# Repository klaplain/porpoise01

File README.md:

# UnderwaterAcoustics
This is the code required for the Underwater Acoustics STM32 Acquisition SubSystem that works with the Porpoise01 board and the Raspberry Pi

main.c contains the necessary code to acquire an analog signal sampling at about 700kHz and storing the result to a .DAT file that contains the analog values.  Although the file has a WAV file header, the values are 16 bit unsigned values so the DAT file needs to be post-processed to convert it to a WAV file.  This post-processing is done when saving to the raspberry pi.

*.ioc contains all the necessary CubeIDE configuration data

uw_acoust_client.py is the app that runs on the raspberry pi and controls the Seeed STM32 acquisition system

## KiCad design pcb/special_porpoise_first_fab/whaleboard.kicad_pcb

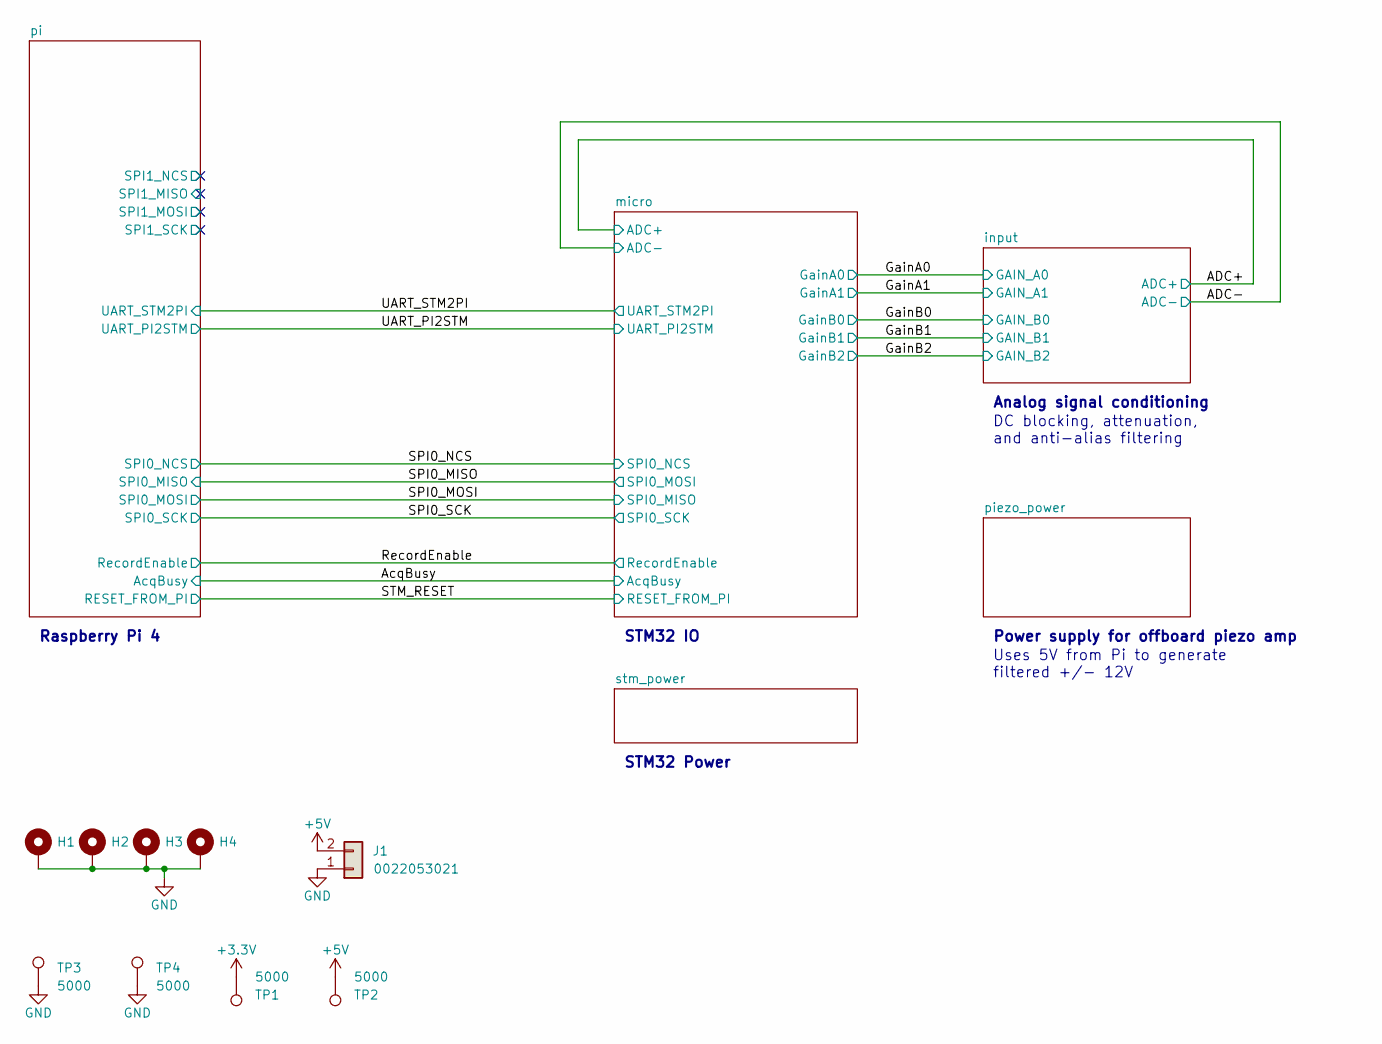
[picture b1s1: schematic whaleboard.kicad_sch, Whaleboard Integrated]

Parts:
H1, H2, H3, H4: MountingHole_Pad; MountingHole_2.7mm_Pad
J1: 0022053021; Molex_KK-254_AE-6410-02A_1x02_P2.54mm_Vertical; DIGI 900-0022053021-ND
TP1, TP2, TP3, TP4: 5000; TestPoint_Keystone_5000-5004_Miniature

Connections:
+3.3V: TP1.1; also elsewhere on the board
+5V: J1.2, TP2.1; also elsewhere on the board
GND: H1.1, H2.1, H3.1, H4.1, J1.1, TP3.1, TP4.1; also elsewhere on the board

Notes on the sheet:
Uses 5V from Pi to generate filtered +/- 12V
Analog signal conditioning
STM32 IO
STM32 Power
DC blocking, attenuation, and anti-alias filtering
Raspberry Pi 4
Power supply for offboard piezo amp

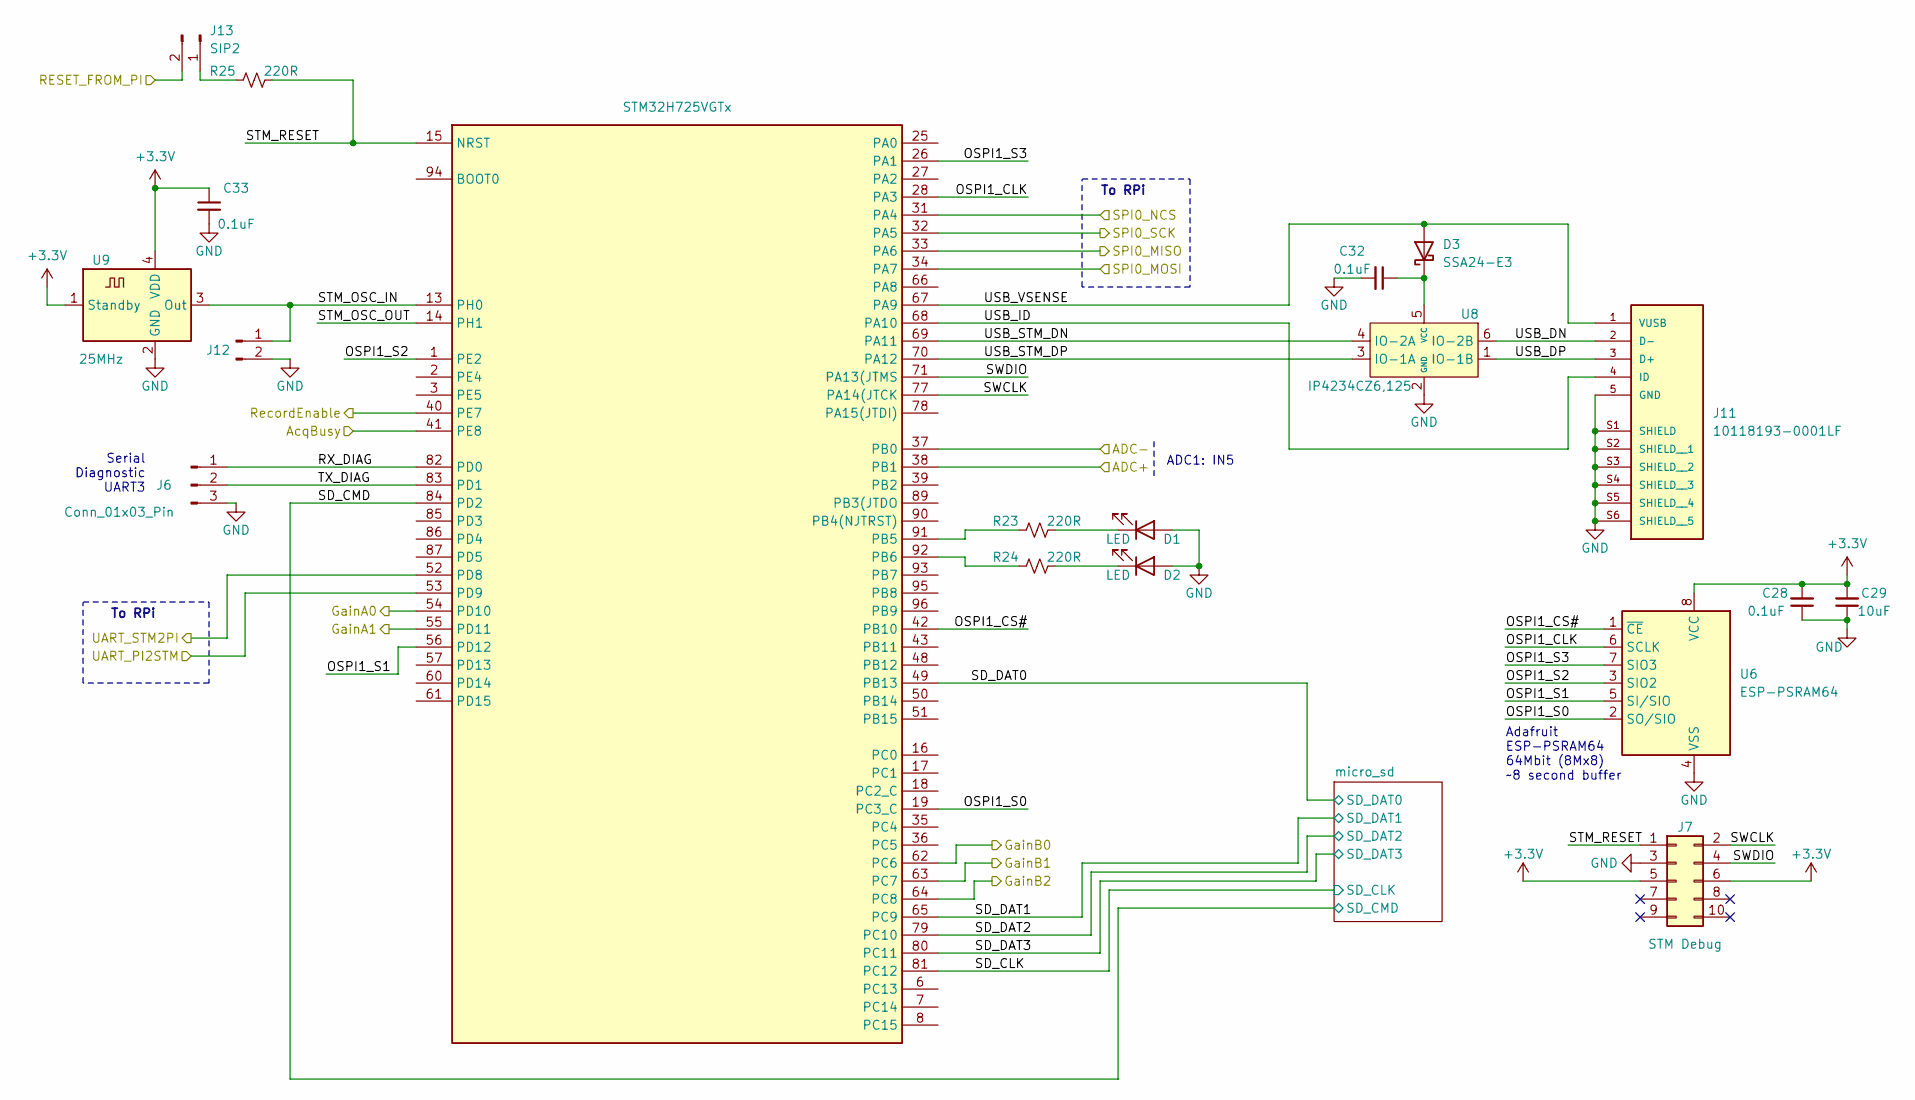
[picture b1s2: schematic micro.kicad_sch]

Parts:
C28, C32, C33: 0.1uF; C_0603_1608Metric; DIGI 1276-1000-1-ND
C29: 10uF; C_0805_2012Metric; DIGI 1276-1096-1-ND
D1, D2: LED; LED_0805_2012Metric; DIGI 3147-B1701UY--20D000214U1930CT-ND
D3: SSA24-E3; D_SMA; DIGI SSA24-E3/61TGICT-ND
J6: Conn_01x03_Pin; PinHeader_1x03_P2.54mm_Vertical
J7: STM Debug; PinSocket_2x05_P2.54mm_Vertical; DIGI S9194-ND
J11: 10118193-0001LF; AMPHENOL_10118193-0001LF; PARTREV E; DIGI 609-4616-1-ND
J12: Conn_01x02_Pin; PinHeader_1x02_P2.00mm_Vertical
J13: SIP2; PinHeader_1x02_P2.54mm_Vertical
R23, R24, R25: 220R; R_0603_1608Metric
U6: ESP-PSRAM64; SOIC-8_3.9x4.9mm_P1.27mm; DIGI 1528-4677-ND
U7: STM32H725VGTx; LQFP-100_14x14mm_P0.5mm
U8: IP4234CZ6,125; TSOP-6_1.65x3.05mm_P0.95mm; DIGI 1727-4717-1-ND
U9: 25MHz; Oscillator_SMD_Abracon_ASDMB-4Pin_2.5x2.0mm; DIGI 535-ATX-H12-F-25.000MHZ-G100-TCT-ND

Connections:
+3.3V: C28.2, C29.2, C33.1, J7.5, J7.6, U6.8 (VCC), U9.1 (Standby), U9.4 (VDD); also elsewhere on the board
/ADC+: U7.38 (PB1); also elsewhere on the board
/ADC-: U7.37 (PB0); also elsewhere on the board
/AcqBusy: U7.41 (PE8); also elsewhere on the board
/GainA0: U7.54 (PD10); also elsewhere on the board
/GainA1: U7.55 (PD11); also elsewhere on the board
/GainB0: U7.62 (PC6); also elsewhere on the board
/GainB1: U7.63 (PC7); also elsewhere on the board
/GainB2: U7.64 (PC8); also elsewhere on the board
/RecordEnable: U7.40 (PE7); also elsewhere on the board
/SPI0_MISO: U7.34 (PA7); also elsewhere on the board
/SPI0_MOSI: U7.33 (PA6); also elsewhere on the board
/SPI0_NCS: U7.31 (PA4); also elsewhere on the board
/SPI0_SCK: U7.32 (PA5); also elsewhere on the board
/STM_RESET: J13.2; also elsewhere on the board
/UART_PI2STM: U7.53 (PD9); also elsewhere on the board
/UART_STM2PI: U7.52 (PD8); also elsewhere on the board
/micro/OSPI1_CLK: U6.6 (SCLK), U7.28 (PA3)
/micro/OSPI1_CS#: U6.1 (~CE), U7.42 (PB10)
/micro/OSPI1_S0: U6.2 (SO/SIO), U7.19 (PC3_C)
/micro/OSPI1_S1: U6.5 (SI/SIO), U7.56 (PD12)
/micro/OSPI1_S2: U6.3 (SIO2), U7.1 (PE2)
/micro/OSPI1_S3: U6.7 (SIO3), U7.26 (PA1)
/micro/RX_DIAG: J6.1, U7.82 (PD0)
/micro/SD_CLK: U7.81 (PC12); also elsewhere on the board
/micro/SD_CMD: U7.84 (PD2); also elsewhere on the board
/micro/SD_DAT0: U7.49 (PB13); also elsewhere on the board
/micro/SD_DAT1: U7.65 (PC9); also elsewhere on the board
/micro/SD_DAT2: U7.79 (PC10); also elsewhere on the board
/micro/SD_DAT3: U7.80 (PC11); also elsewhere on the board
/micro/STM_OSC_IN: J12.1, U7.13 (PH0), U9.3 (Out)
/micro/STM_OSC_OUT: U7.14 (PH1)
/micro/STM_RESET: J7.1, R25.2, U7.15 (NRST)
/micro/SWCLK: J7.2, U7.77 (PA14(JTCK)
/micro/SWDIO: J7.4, U7.71 (PA13(JTMS)
/micro/TX_DIAG: J6.2, U7.83 (PD1)
/micro/USB_DN: J11.2 (D-), U8.6 (IO-2B)
/micro/USB_DP: J11.3 (D+), U8.1 (IO-1B)
/micro/USB_ID: J11.4 (ID), U7.68 (PA10)
/micro/USB_STM_DN: U7.69 (PA11), U8.4 (IO-2A)
/micro/USB_STM_DP: U7.70 (PA12), U8.3 (IO-1A)
/micro/USB_VSENSE: D3.2 (A), J11.1 (VUSB), U7.67 (PA9)
GND: C28.1, C29.1, C32.2, C33.2, D1.2 (A), D2.2 (A), J6.3, J7.3, J11.5 (GND), J11.S1 (SHIELD), J11.S2 (SHIELD__1), J11.S3 (SHIELD__2), J11.S4 (SHIELD__3), J11.S5 (SHIELD__4), J11.S6 (SHIELD__5), J12.2, U6.4 (VSS), U8.2 (GND), U9.2 (GND); also elsewhere on the board
unnamed: D1.1 (K), R23.2
unnamed: D2.1 (K), R24.2
unnamed: C32.1, D3.1 (K), U8.5 (VCC)
unnamed: J13.1, R25.1
unnamed: R23.1, U7.91 (PB5)
unnamed: R24.1, U7.92 (PB6)

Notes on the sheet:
Adafruit ESP-PSRAM64 64Mbit (8Mx8) ~8 second buffer
Serial Diagnostic UART3
ADC1: IN5
To RPi

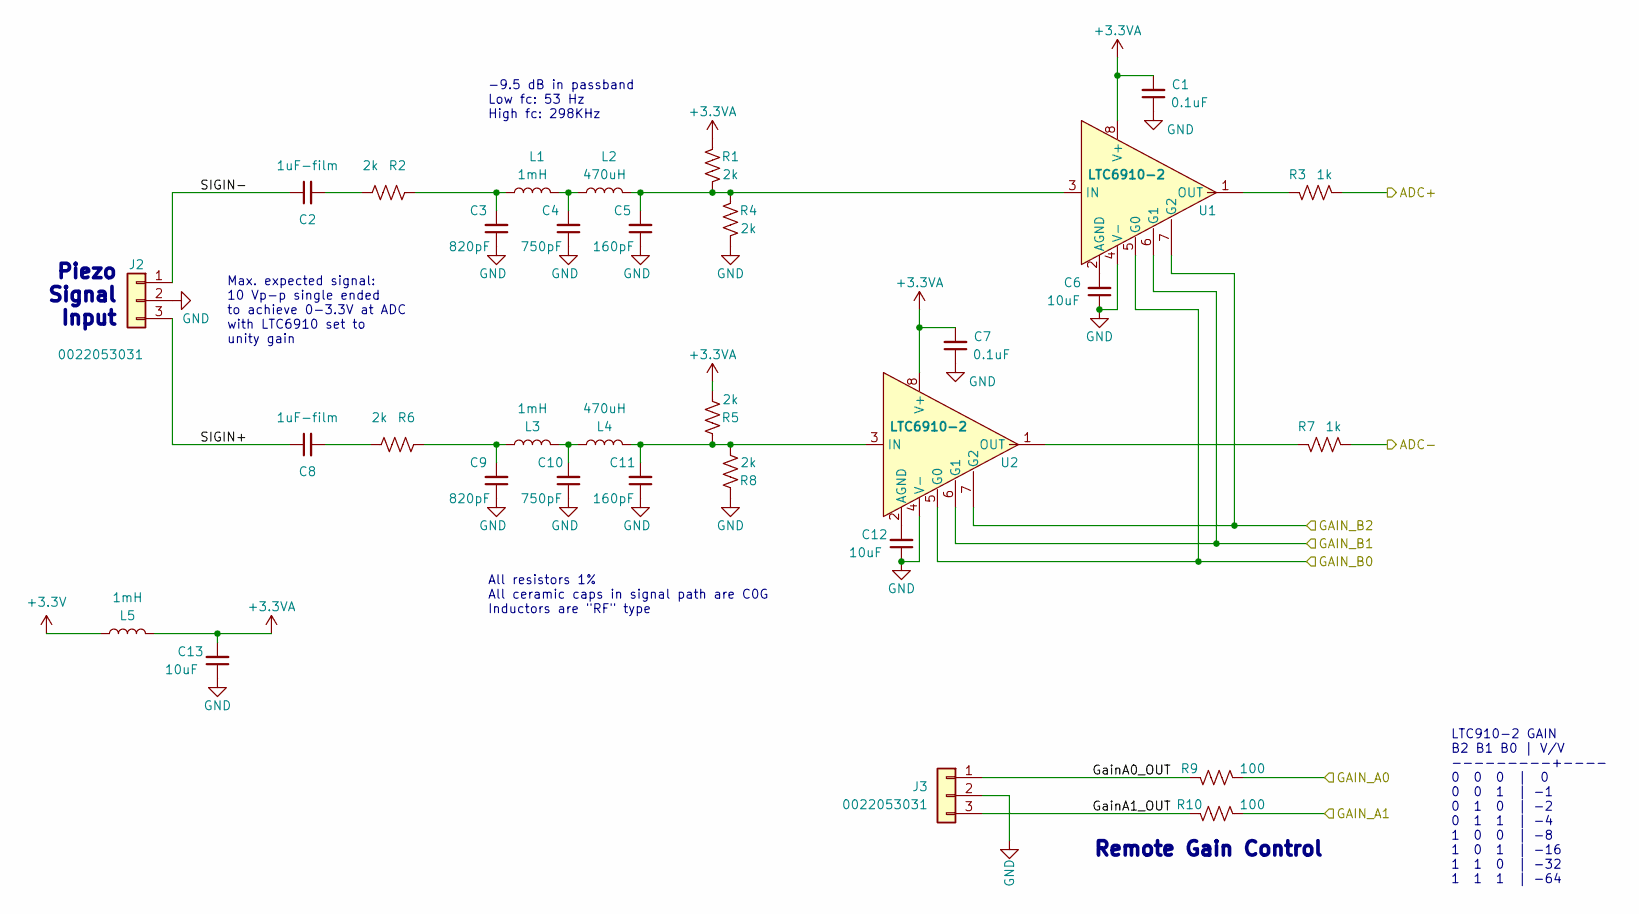
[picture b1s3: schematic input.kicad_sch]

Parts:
C1, C7: 0.1uF; C_0603_1608Metric; DIGI 1276-1000-1-ND
C2, C8: 1uF-film; C_2220_5750Metric; DIGI 399-LDECD4100MA0N00CT-ND
C3, C9: 820pF; C_1206_3216Metric; DIGI 478-KGM31BCG2A821JTCT-ND
C4, C10: 750pF; C_1206_3216Metric; DIGI 399-14711-1-ND
C5, C11: 160pF; C_0603_1608Metric; DIGI 399-15367-1-ND
C6, C12, C13: 10uF; C_0805_2012Metric; DIGI 1276-1096-1-ND
J2, J3: 0022053031; CONN_A-7478-03A_MOL; DIGI WM4301-ND
L1, L3, L5: 1mH; L_1812_4532Metric_Pad1.30x3.40mm_HandSolder; DIGI CM453232-102JLCT-ND
L2, L4: 470uH; L_1812_4532Metric_Pad1.30x3.40mm_HandSolder; DIGI 118-CM453232-471JLCT-ND
R1, R2, R4, R5, R6, R8: 2k; R_0603_1608Metric; DIGI RC0603FR-072KL
R3, R7: 1k; R_0603_1608Metric; DIGI 311-1.00KHRCT-ND
R9, R10: 100; R_0603_1608Metric; DIGI 311-100HRCT-ND
U1, U2: LTC6910-2; TSOT-23-8; DIGI 161-LTC6910-2ITS8#TRPBFCT-ND

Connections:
+3.3V: L5.1; also elsewhere on the board
+3.3VA: C1.2, C7.2, C13.2, L5.2, R1.2, R5.1, U1.8 (V+), U2.8 (V+)
/ADC+: R3.1; also elsewhere on the board
/ADC-: R7.1; also elsewhere on the board
/GainA0: R9.1; also elsewhere on the board
/GainA1: R10.1; also elsewhere on the board
/GainB0: U1.5 (G0), U2.5 (G0); also elsewhere on the board
/GainB1: U1.6 (G1), U2.6 (G1); also elsewhere on the board
/GainB2: U1.7 (G2), U2.7 (G2); also elsewhere on the board
/input/GainA0_OUT: J3.1, R9.2
/input/GainA1_OUT: J3.3, R10.2
/input/SIGIN+: C8.1, J2.3
/input/SIGIN-: C2.1, J2.1
GND: C1.1, C3.1, C4.1, C5.1, C6.1, C7.1, C9.1, C10.1, C11.1, C12.1, C13.1, J2.2, J3.2, R4.1, R8.2, U1.4 (V-), U2.4 (V-); also elsewhere on the board
unnamed: C2.2, R2.1
unnamed: C3.2, L1.1, R2.2
unnamed: C4.2, L1.2, L2.1
unnamed: C8.2, R6.1
unnamed: C9.2, L3.1, R6.2
unnamed: C10.2, L3.2, L4.1
unnamed: C6.2, U1.2 (AGND)
unnamed: C5.2, L2.2, R1.1, R4.2, U1.3 (IN)
unnamed: R3.2, U1.1 (OUT)
unnamed: C12.2, U2.2 (AGND)
unnamed: C11.2, L4.2, R5.2, R8.1, U2.3 (IN)
unnamed: R7.2, U2.1 (OUT)

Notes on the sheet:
All resistors 1% All ceramic caps in signal path are C0G Inductors are "RF" type
-9.5 dB in passband Low fc: 53 Hz High fc: 298KHz
Max. expected signal: 10 Vp-p single ended to achieve 0-3.3V at ADC with LTC6910 set to unity gain
LTC910-2 GAIN B2 B1 B0 | V/V ---------+---- 0 0 0 | 0 0 0 1 | -1 0 1 0 | -2 0 1 1 | -4 1 0 0 | -8 1 0 1 | -16 1 1 0 | -32 1 1 1 | -64
Piezo Signal Input
Remote Gain Control

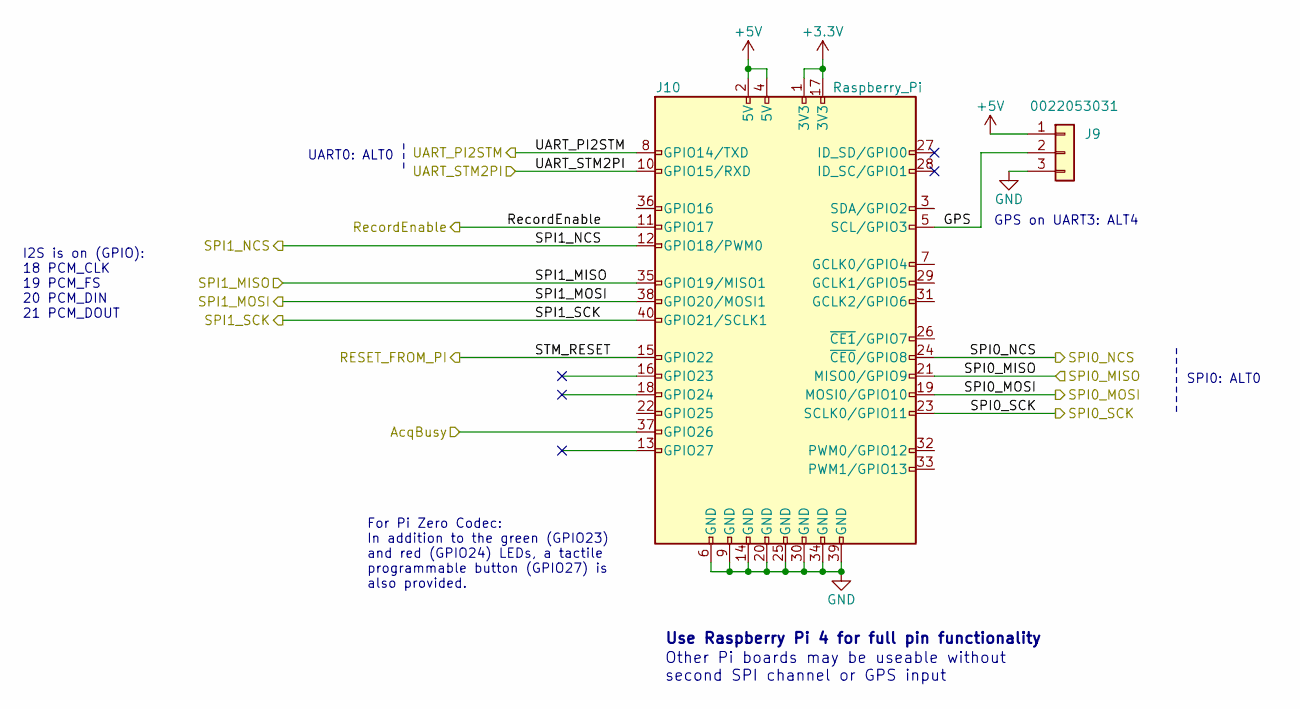
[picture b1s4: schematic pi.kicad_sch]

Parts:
J9: 0022053031; CONN_A-7478-03A_MOL; DIGI WM4301-ND
J10: Raspberry_Pi; PinSocket_2x20_P2.54mm_Vertical; DIGI 1568-PRT-16763-ND

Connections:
+3.3V: J10.1 (3V3), J10.17 (3V3); also elsewhere on the board
+5V: J9.1, J10.2 (5V), J10.4 (5V); also elsewhere on the board
/AcqBusy: J10.37 (GPIO26); also elsewhere on the board
/RecordEnable: J10.11 (GPIO17); also elsewhere on the board
/SPI0_MISO: J10.21 (MISO0/GPIO9); also elsewhere on the board
/SPI0_MOSI: J10.19 (MOSI0/GPIO10); also elsewhere on the board
/SPI0_NCS: J10.24 (~CE0/GPIO8); also elsewhere on the board
/SPI0_SCK: J10.23 (SCLK0/GPIO11); also elsewhere on the board
/STM_RESET: J10.15 (GPIO22); also elsewhere on the board
/UART_PI2STM: J10.8 (GPIO14/TXD); also elsewhere on the board
/UART_STM2PI: J10.10 (GPIO15/RXD); also elsewhere on the board
/pi/GPS: J9.2, J10.5 (SCL/GPIO3)
/pi/SPI1_MISO: J10.35 (GPIO19/MISO1)
/pi/SPI1_MOSI: J10.38 (GPIO20/MOSI1)
/pi/SPI1_NCS: J10.12 (GPIO18/PWM0)
/pi/SPI1_SCK: J10.40 (GPIO21/SCLK1)
GND: J9.3, J10.6 (GND), J10.9 (GND), J10.14 (GND), J10.20 (GND), J10.25 (GND), J10.30 (GND), J10.34 (GND), J10.39 (GND); also elsewhere on the board

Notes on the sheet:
Other Pi boards may be useable without second SPI channel or GPS input
Use Raspberry Pi 4 for full pin functionality
SPI0: ALT0
I2S is on (GPIO): 18 PCM_CLK 19 PCM_FS 20 PCM_DIN 21 PCM_DOUT
UART0: ALT0
GPS on UART3: ALT4
For Pi Zero Codec: In addition to the green (GPIO23) and red (GPIO24) LEDs, a tactile programmable button (GPIO27) is also provided.

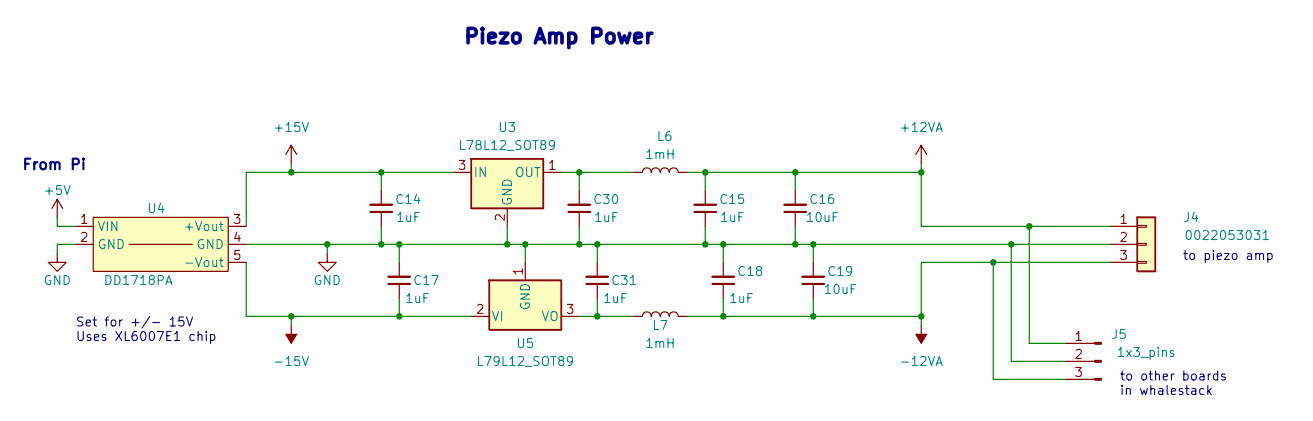
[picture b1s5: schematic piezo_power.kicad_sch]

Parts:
C14, C15, C17, C18, C30, C31: 1uF; C_0603_1608Metric; DIGI 1276-1102-1-ND
C16, C19: 10uF; C_0805_2012Metric; DIGI 1276-1096-1-ND
J4: 0022053031; CONN_A-7478-03A_MOL; DIGI WM4301-ND
J5: 1x3_pins; PinHeader_1x03_P2.54mm_Vertical
L6, L7: 1mH; L_1812_4532Metric_Pad1.30x3.40mm_HandSolder; DIGI CM453232-102JLCT-ND
U3: L78L12_SOT89; SOT-89-3; DIGI 497-1195-1-ND
U4: DD1718PA
U5: L79L12_SOT89; SOT-89-3; DIGI 497-7301-1-ND

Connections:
+5V: U4.1 (VIN); also elsewhere on the board
+12VA: C15.2, C16.2, J4.1, J5.1, L6.2
+15V: C14.2, U3.3 (IN), U4.3 (+Vout)
-12VA: C18.1, C19.1, J4.3, J5.3, L7.2
-15V: C17.1, U4.5 (-Vout), U5.2 (VI)
GND: C14.1, C15.1, C16.1, C17.2, C18.2, C19.2, C30.1, C31.2, J4.2, J5.2, U3.2 (GND), U4.2 (GND), U4.4 (GND), U5.1 (GND); also elsewhere on the board
unnamed: C30.2, L6.1, U3.1 (OUT)
unnamed: C31.1, L7.1, U5.3 (VO)

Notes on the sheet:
From Pi
to piezo amp
Piezo Amp Power
Set for +/- 15V Uses XL6007E1 chip
to other boards in whalestack

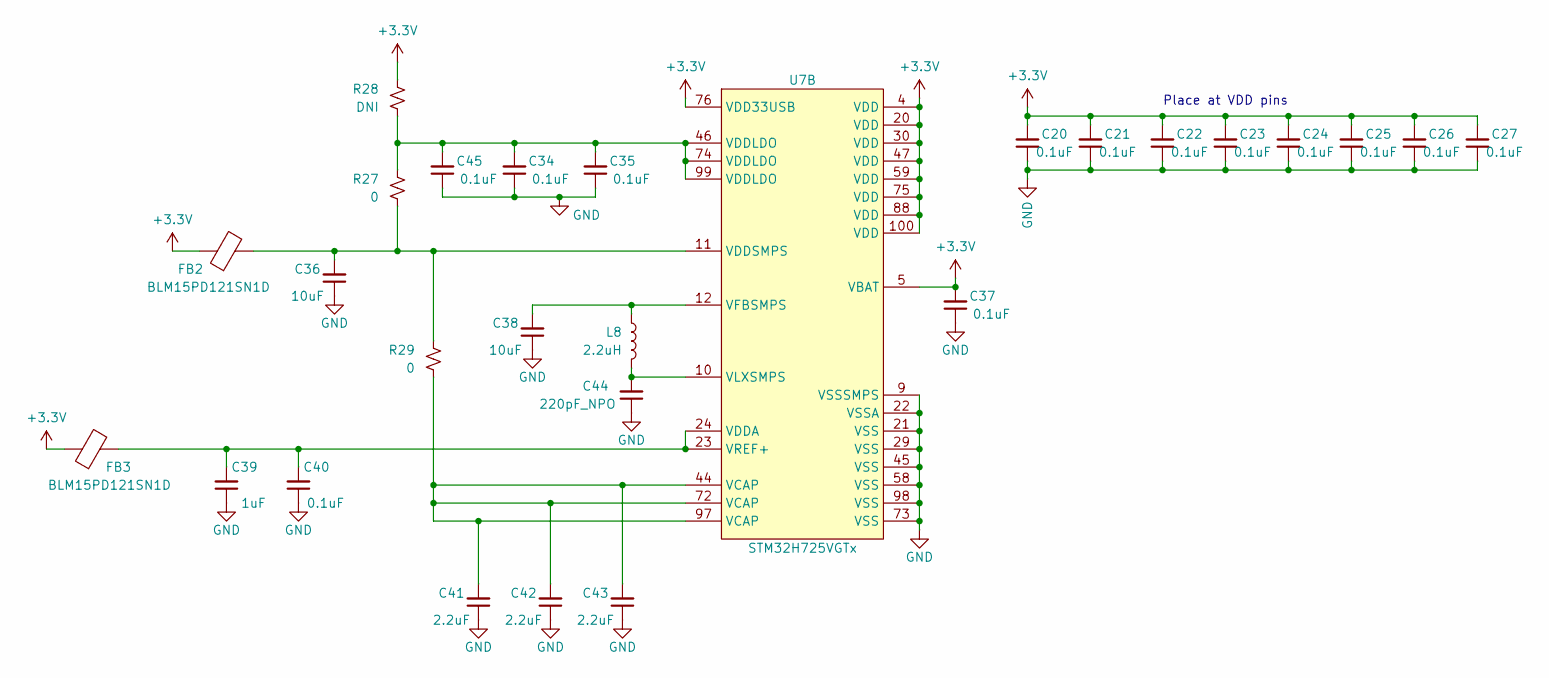
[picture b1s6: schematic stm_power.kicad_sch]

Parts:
C20, C21, C22, C23, C24, C25, C26, C27, C34, C35, C37, C40, C45: 0.1uF; C_0603_1608Metric; DIGI 1276-1000-1-ND
C36, C38: 10uF; C_0805_2012Metric; DIGI 1276-1096-1-ND
C39: 1uF; C_0603_1608Metric; DIGI 1276-1102-1-ND
C41, C42, C43: 2.2uF; C_0805_2012Metric; DIGI 1276-1763-1-ND
C44: 220pF_NPO; C_0603_1608Metric; DIGI 1276-1008-1-ND
FB2, FB3: BLM15PD121SN1D; C_0402_1005Metric_Pad0.74x0.62mm_HandSolder; DIGI 490-5203-1-ND
L8: 2.2uH; L_1008_2520Metric; DIGI 490-5114-1-ND
R27, R29: 0; R_0402_1005Metric_Pad0.72x0.64mm_HandSolder
R28: DNI; R_0402_1005Metric_Pad0.72x0.64mm_HandSolder
U7: STM32H725VGTx; LQFP-100_14x14mm_P0.5mm

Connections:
+3.3V: C20.2, C21.2, C22.2, C23.2, C24.2, C25.2, C26.2, C27.2, C37.2, FB2.1, FB3.1, R28.1, U7.4 (VDD), U7.5 (VBAT), U7.20 (VDD), U7.30 (VDD), U7.47 (VDD), U7.59 (VDD), U7.75 (VDD), U7.76 (VDD33USB), U7.88 (VDD), U7.100 (VDD); also elsewhere on the board
GND: C20.1, C21.1, C22.1, C23.1, C24.1, C25.1, C26.1, C27.1, C34.1, C35.1, C36.1, C37.1, C38.1, C39.1, C40.1, C41.1, C42.1, C43.1, C44.1, C45.1, U7.9 (VSSSMPS), U7.21 (VSS), U7.22 (VSSA), U7.29 (VSS), U7.45 (VSS), U7.58 (VSS), U7.73 (VSS), U7.98 (VSS); also elsewhere on the board
unnamed: C34.2, C35.2, C45.2, R27.1, R28.2, U7.46 (VDDLDO), U7.74 (VDDLDO), U7.99 (VDDLDO)
unnamed: C41.2, C42.2, C43.2, R29.2, U7.44 (VCAP), U7.72 (VCAP), U7.97 (VCAP)
unnamed: C39.2, C40.2, FB3.2, U7.23 (VREF+), U7.24 (VDDA)
unnamed: C36.2, FB2.2, R27.2, R29.1, U7.11 (VDDSMPS)
unnamed: C38.2, L8.2, U7.12 (VFBSMPS)
unnamed: C44.2, L8.1, U7.10 (VLXSMPS)

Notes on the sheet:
Place at VDD pins

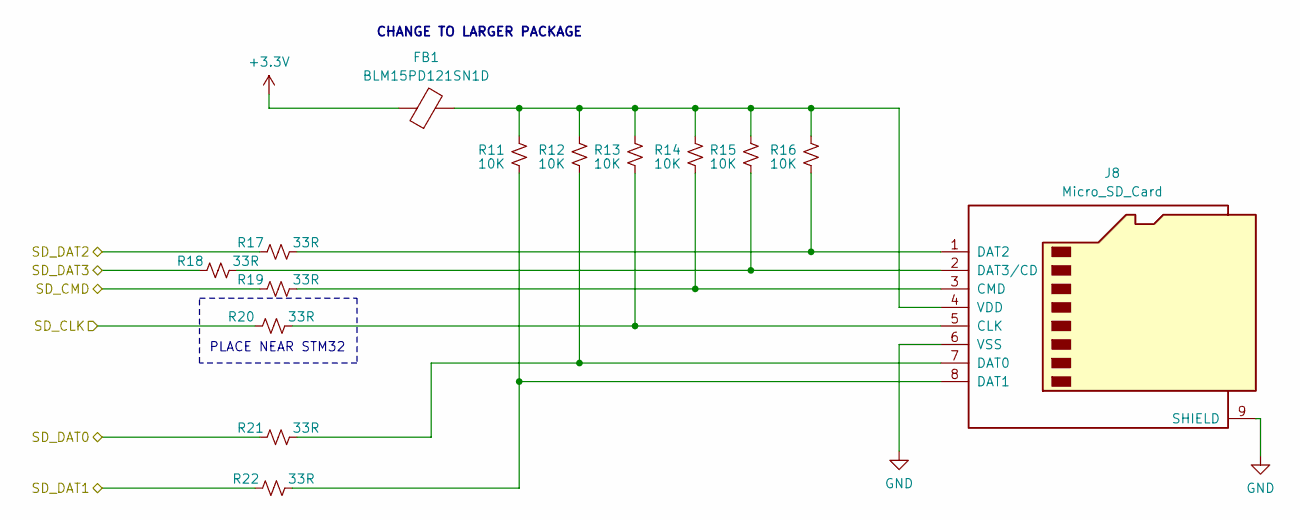
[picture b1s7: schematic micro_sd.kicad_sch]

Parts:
FB1: BLM15PD121SN1D; C_0402_1005Metric_Pad0.74x0.62mm_HandSolder; DIGI 490-5203-1-ND
J8: Micro_SD_Card; MOLEX_47219-2001; DIGI WM6698CT-ND
R11, R12, R13, R14, R15, R16: 10K; R_0603_1608Metric; DIGI 311-10.0KHRCT-ND
R17, R18, R19, R20, R21, R22: 33R; R_0603_1608Metric; DIGI 13-RC0603FR-1333RLCT-ND

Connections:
+3.3V: FB1.1; also elsewhere on the board
/micro/SD_CLK: R20.1; also elsewhere on the board
/micro/SD_CMD: R19.1; also elsewhere on the board
/micro/SD_DAT0: R21.1; also elsewhere on the board
/micro/SD_DAT1: R22.1; also elsewhere on the board
/micro/SD_DAT2: R17.1; also elsewhere on the board
/micro/SD_DAT3: R18.1; also elsewhere on the board
GND: J8.6 (VSS), J8.9 (SHIELD); also elsewhere on the board
unnamed: J8.5 (CLK), R13.1, R20.2
unnamed: J8.3 (CMD), R14.1, R19.2
unnamed: J8.7 (DAT0), R12.1, R21.2
unnamed: J8.8 (DAT1), R11.1, R22.2
unnamed: J8.1 (DAT2), R16.1, R17.2
unnamed: J8.2 (DAT3/CD), R15.1, R18.2
unnamed: FB1.2, J8.4 (VDD), R11.2, R12.2, R13.2, R14.2, R15.2, R16.2

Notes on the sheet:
CHANGE TO LARGER PACKAGE
PLACE NEAR STM32

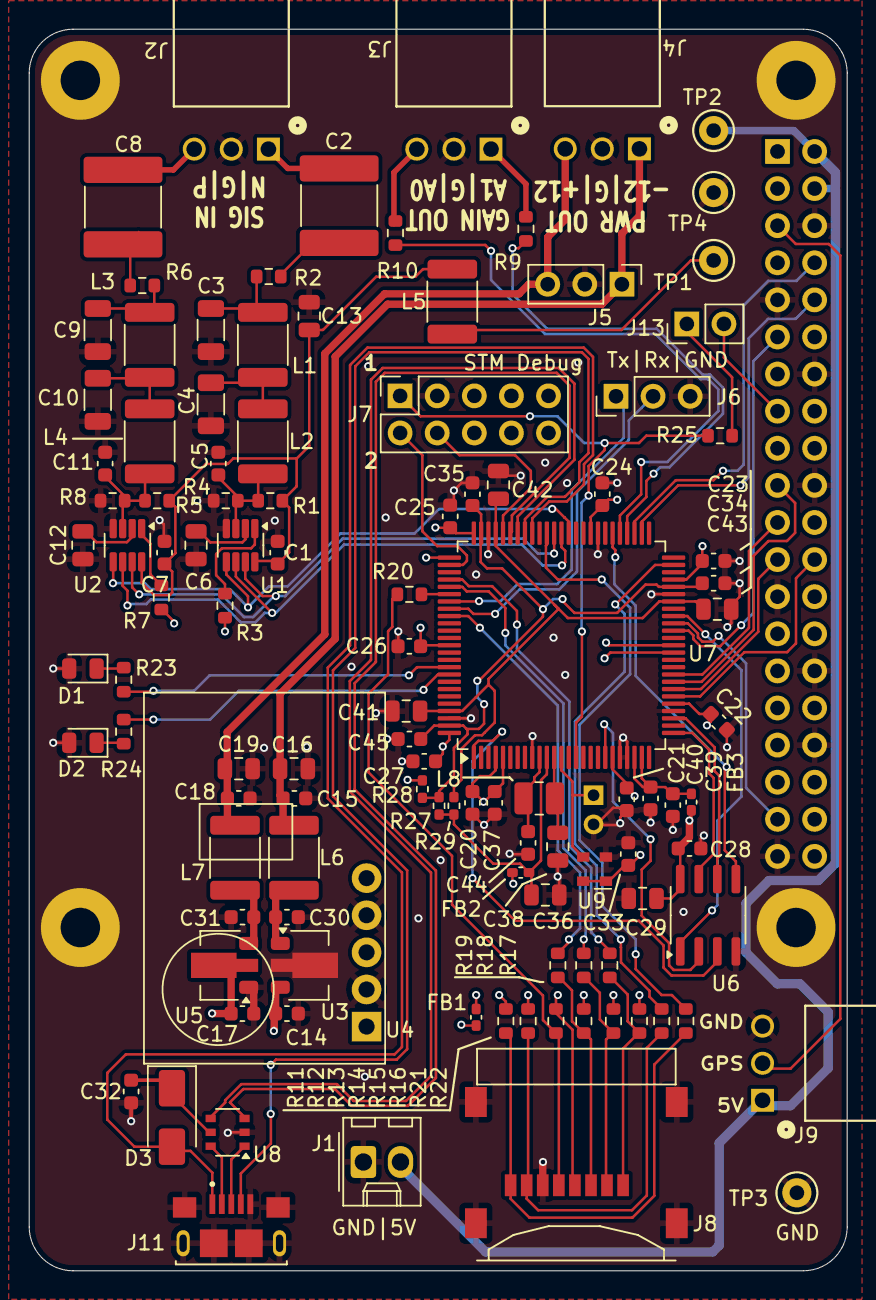
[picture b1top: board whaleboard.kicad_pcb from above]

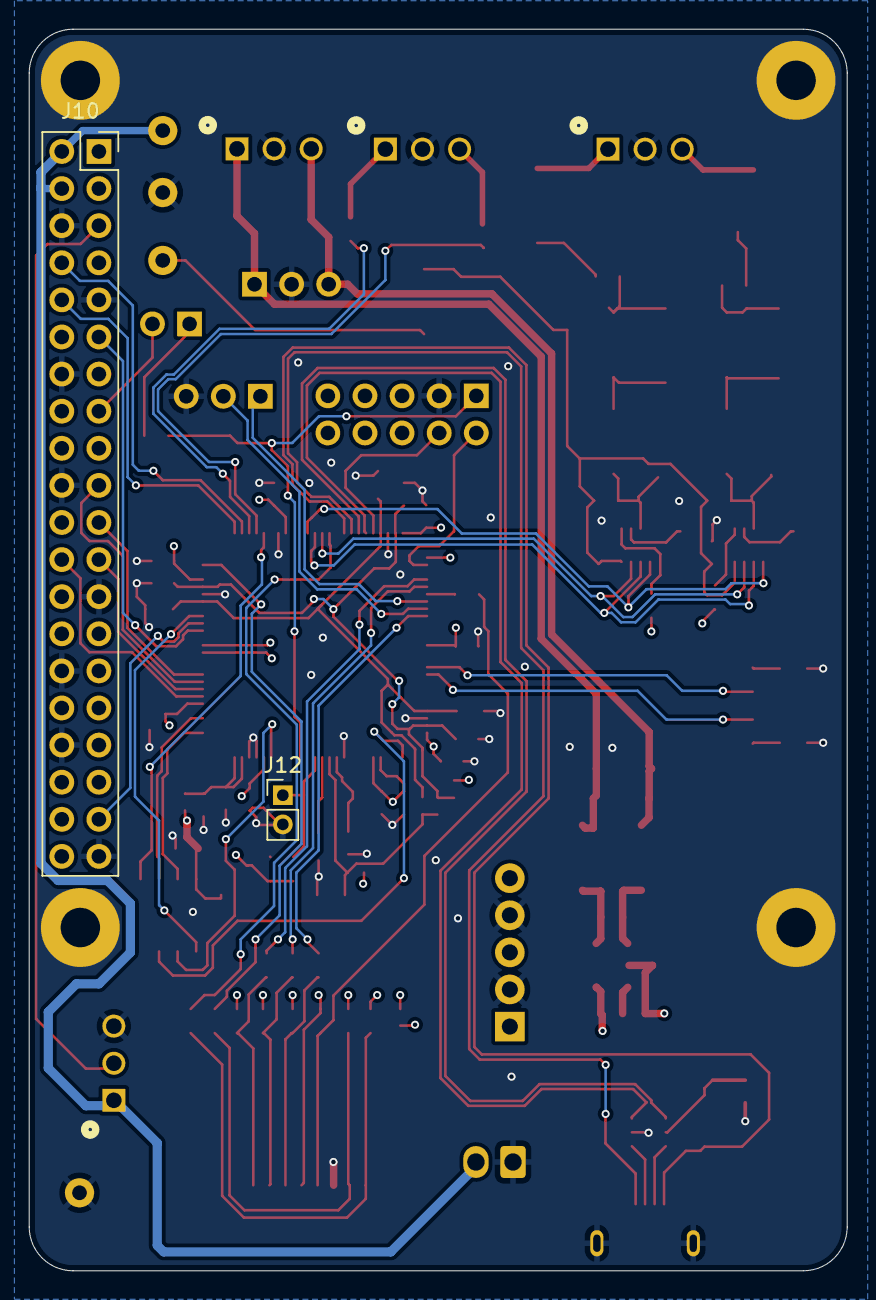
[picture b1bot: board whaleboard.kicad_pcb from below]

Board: 4 copper layers, 56.0 x 85.0 mm, 117 parts (2 on the bottom side), 86 nets.

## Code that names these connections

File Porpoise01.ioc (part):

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Mcu.Name=STM32H725VGTx
Mcu.Package=LQFP100
Mcu.UserName=STM32H725VGTx
PA0.GPIOParameters=GPIO_PuPd,GPIO_Label
PA0.GPIO_Label=SD_Card_Detect
PA0.GPIO_PuPd=GPIO_PULLDOWN
PA0.Signal=GPIO_Input
PA4.GPIOParameters=GPIO_Speed
PA4.GPIO_Speed=GPIO_SPEED_FREQ_HIGH
PA4.Mode=NSS_Signal_Hard_Input
PA4.Signal=SPI6_NSS
PA5.GPIOParameters=GPIO_Speed
PA5.GPIO_Speed=GPIO_SPEED_FREQ_HIGH
PA5.Mode=Full_Duplex_Slave
PA5.Signal=SPI6_SCK
PA6.GPIOParameters=GPIO_Speed
PA6.GPIO_Speed=GPIO_SPEED_FREQ_HIGH
PA6.Mode=Full_Duplex_Slave
PA6.Signal=SPI6_MISO
PA7.GPIOParameters=GPIO_Speed,GPIO_PuPd
PA7.GPIO_PuPd=GPIO_NOPULL
PA7.GPIO_Speed=GPIO_SPEED_FREQ_HIGH
PA7.Mode=Full_Duplex_Slave
PA7.Signal=SPI6_MOSI
PB0.Signal=ADCx_INN5
PB1.Signal=ADCx_INP5
PB13.Mode=SD_4_bits_Wide_bus
PB13.Signal=SDMMC1_D0
PB5.GPIOParameters=GPIO_Label
PB5.GPIO_Label=RED_LED
PB5.Signal=GPIO_Output
PB6.GPIOParameters=GPIO_Speed,GPIO_Label
PB6.GPIO_Label=Orange_LED
PB6.GPIO_Speed=GPIO_SPEED_FREQ_HIGH
PB6.Signal=GPIO_Output
PC10.Mode=SD_4_bits_Wide_bus
PC10.Signal=SDMMC1_D2
PC11.Mode=SD_4_bits_Wide_bus
PC11.Signal=SDMMC1_D3
PC12.Mode=SD_4_bits_Wide_bus
PC12.Signal=SDMMC1_CK
PC14-OSC32_IN.Mode=LSE-External-Oscillator
PC14-OSC32_IN.Signal=RCC_OSC32_IN
PC15-OSC32_OUT.Mode=LSE-External-Oscillator
PC15-OSC32_OUT.Signal=RCC_OSC32_OUT
PC6.GPIOParameters=GPIO_Label
PC6.GPIO_Label=GAINB0
PC6.Signal=GPIO_Output
PC7.GPIOParameters=GPIO_Label
PC7.GPIO_Label=GAINB1
PC7.Signal=GPIO_Output
PC8.GPIOParameters=GPIO_Label
PC8.GPIO_Label=GAINB2
PC8.Signal=GPIO_Output
PC9.Mode=SD_4_bits_Wide_bus
PC9.Signal=SDMMC1_D1
PD0.Mode=Asynchronous
PD0.Signal=UART4_RX
PD1.Mode=Asynchronous
PD1.Signal=UART4_TX
PD10.GPIOParameters=GPIO_Label
PD10.GPIO_Label=GAINA0
PD10.Signal=GPIO_Output
PD11.GPIOParameters=GPIO_Label
PD11.GPIO_Label=GAINA1
PD11.Signal=GPIO_Output
PD2.Mode=SD_4_bits_Wide_bus
PD2.Signal=SDMMC1_CMD
PD8.Mode=Asynchronous
PD8.Signal=USART3_TX
PD9.Mode=Asynchronous
PD9.Signal=USART3_RX
PE7.GPIOParameters=GPIO_Label
PE7.GPIO_Label=RecordEnable
PE7.Signal=GPIO_Output
PE8.GPIOParameters=GPIO_Label
PE8.GPIO_Label=Acq_Busy
PE8.Signal=GPIO_Output
PH0-OSC_IN.Mode=HSE-External-Oscillator
PH0-OSC_IN.Signal=RCC_OSC_IN
PH1-OSC_OUT.Mode=HSE-External-Oscillator
PH1-OSC_OUT.Signal=RCC_OSC_OUT
RCC.SYSCLKFreq_VALUE=500000000
RCC.SYSCLKSource=RCC_SYSCLKSOURCE_PLLCLK
board=custom

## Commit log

2025-06-22 Gain setup x1 with UART4 debug working
2025-06-23 SD Card Directory read working
2025-06-29 SPI6 Support
    SPI operating at a basic level. Receiving commands from raspi in form of >TIM for example. Sets time correctly and can initiate a directory request (but not process yet)
2025-06-30 Works with 6/29/2025 main software
    This IOC supports SD card, UART4, SPI6. It is configured for the ADC but not tests
2025-06-30 Create UAserver.py
    This works with the porpoise01. It can set the date/time and get the directory list. It does not yet support the ADC/Acquisition and also does not control the gain of the porpoise 01 or of the pre-amp
2025-06-30 Onboard amplifier gain support
    Now correctly sets gain based in B0,B1,B2.
2025-07-01 Support for DAT file transfer to Pi
    Supports acquisition, transfer to Pi and Analyze
2025-07-01 Support for continuous DMA
    Now supports acquisition and data transfer to pi
2025-07-01 LED support for download transaction
    One LED shows command download from Pi and One LED for ADC overrun. Using Record Enable pin to report when ADC buffer is full/switched (used to check ADC convert rate)
2025-07-07 Support for WAV file download
2025-07-09 Rename UAserver.py to raspi/UAserver.py
2025-07-09 Rename RASPI STM Protocol Rev 2 (1).pptx to Documentation/RASPI STM Protocol Rev 2 (1).pptx
2025-07-09 Raspberry Pi
2025-07-09 Commit flask and UAServer code
2025-11-06 Add initial Kicad files list
2025-11-06 kiCad files for whaleboard
